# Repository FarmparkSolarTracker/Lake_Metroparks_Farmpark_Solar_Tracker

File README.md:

# Lake_Metroparks_Farmpark_Solar_Tracker
For more information, please see the wiki [here](https://github.com/FarmparkSolarTracker/Lake_Metroparks_Farmpark_Solar_Tracker/wiki).  

# Things which need work:
* Possible board issue where one side of the H-Bridges is unable to pull low, it only reaches High-Impedance
* Software for board is in a preliminary version, has not been fully tested due to the above issue
* A rough tester board has been included in the box, which theoretically can be used to send RS-485 commands to the main PCB. Code needs to be written for this device
* If the park has not done it yet, a new motor for the azimuth system must be ordered (it is believed that the worm gear is broken)
* The elevation linear actuator must be clamped in place
* Grommets must be put in place on the cables entering the new box
* Better data should be collected from the sensor, to better know how it operates

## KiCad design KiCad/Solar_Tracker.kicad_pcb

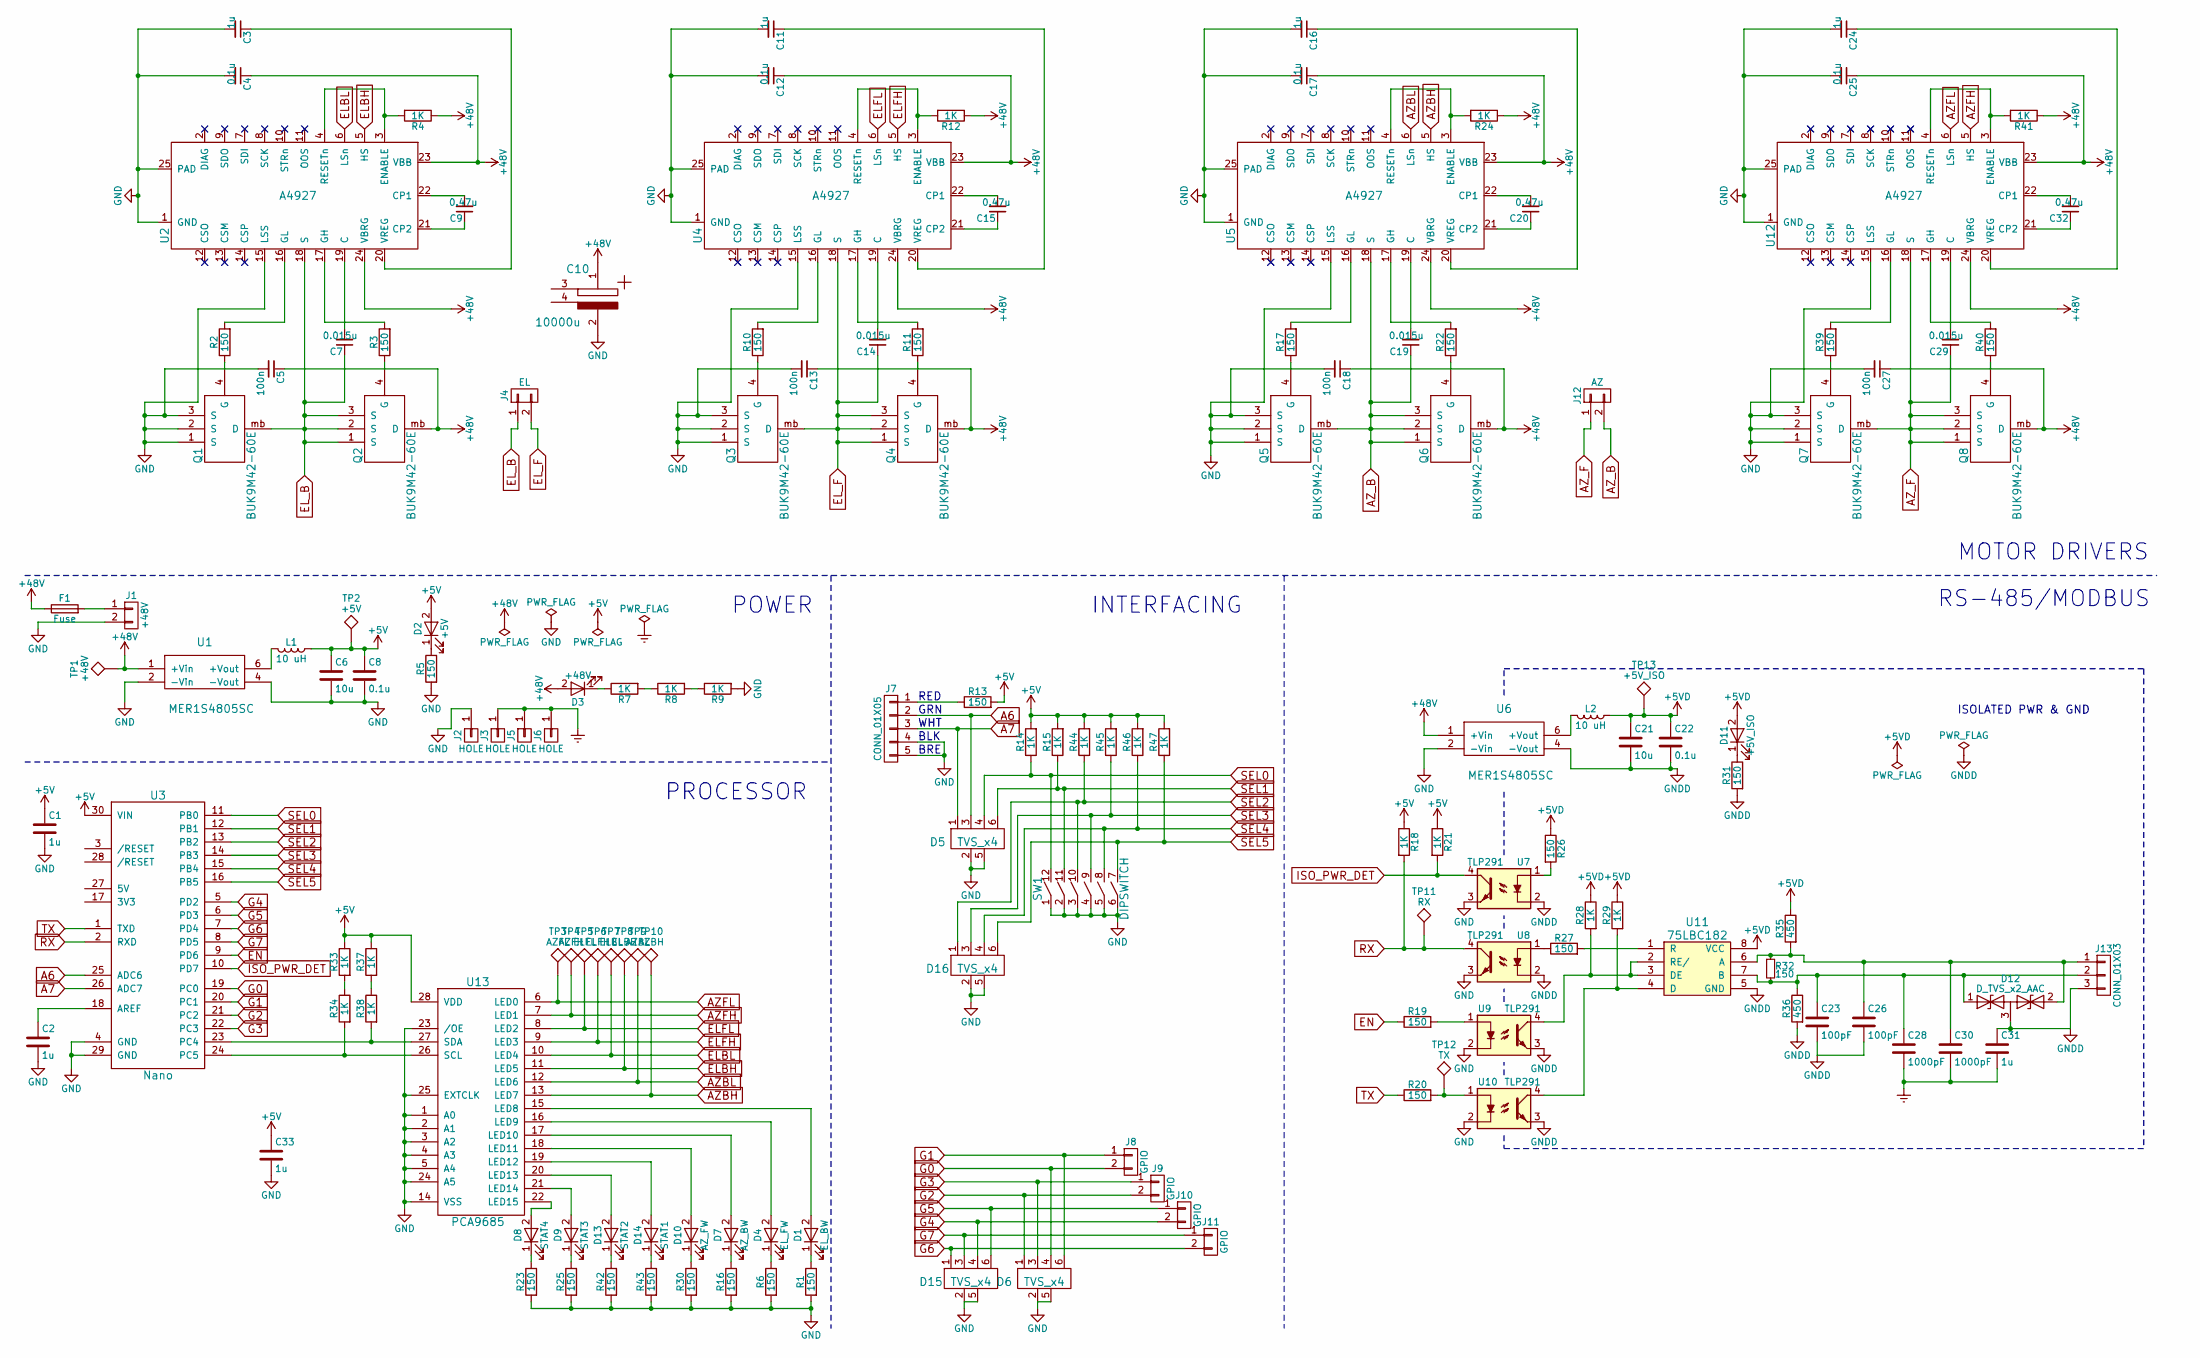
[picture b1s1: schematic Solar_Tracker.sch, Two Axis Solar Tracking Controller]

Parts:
C1, C2, C3, C11, C16, C24, C31, C33: 1u; C_0805
C4, C8, C12, C17, C22, C25: 0.1u; C_0805
C5, C13, C18, C27: 100n; C_0805
C6, C21: 10u; C_0805
C7, C14, C19, C29: 0.015u; C_0805
C9, C15, C20, C32: 0.47u; C_0805
C10: 10000u; vnd_cap
C23, C26: 100pF; C_0805
C28, C30: 1000pF; C_0805
D1: EL_BW; LED_1206_HandSoldering
D2: +5V; LED_1206_HandSoldering
D3: +48V; LED_1206_HandSoldering
D4: EL_FW; LED_1206_HandSoldering
D5, D6, D15, D16: TVS_x4; tvs_quad
D7: AZ_BW; LED_1206_HandSoldering
D8: STAT4; LED_1206_HandSoldering
D9: STAT3; LED_1206_HandSoldering
D10: AZ_FW; LED_1206_HandSoldering
D11: +5V_ISO; LED_1206_HandSoldering
D12: D_TVS_x2_AAC; SOT-23
D13: STAT2; LED_1206_HandSoldering
D14: STAT1; LED_1206_HandSoldering
F1: Fuse; R_Axial_DIN0204_L3.6mm_D1.6mm_P5.08mm_Horizontal
J1: +48V; PhoenixContact_GMSTBVA-G_02x7.50mm_Vertical
J2, J3, J5, J6: HOLE; M3
J4: EL; PhoenixContact_GMSTBVA-G_02x7.50mm_Vertical
J7: CONN_01X05; PhoenixContact_MCV-G_05x5.08mm_Vertical
J8, J9, J10, J11: GPIO; PhoenixContact_GMSTBVA-G_02x7.50mm_Vertical
J12: AZ; PhoenixContact_GMSTBVA-G_02x7.50mm_Vertical
J13: CONN_01X03; PhoenixContact_MCV-G_03x5.08mm_Vertical
L1, L2: 10 uH; L_1206_HandSoldering
Q1, Q2, Q3, Q4, Q5, Q6, Q7, Q8: BUK9M42-60E; nFET
R1, R2, R3, R5, R6, R10, R11, R13, R16, R17, R19, R20, R22, R23, R25, R26, R27, R30, R31, R32, R39, R40, R42, R43: 150; R_0805
R4, R7, R8, R9, R12, R14, R15, R18, R21, R24, R28, R29, R33, R34, R37, R38, R41, R44, R45, R46, R47: 1K; R_0805
R35, R36: 450; R_0805
SW1: DIPSWITCH; DIP-12_W7.62mm
TP1: +48V; test_pad
TP2: +5V; test_pad
TP3: AZFL; test_pad
TP4: AZFH; test_pad
TP5: ELFL; test_pad
TP6: ELFH; test_pad
TP7: ELBL; test_pad
TP8: ELBH; test_pad
TP9: AZBL; test_pad
TP10: AZBH; test_pad
TP11: RX; test_pad
TP12: TX; test_pad
TP13: +5V_ISO; test_pad
U1, U6: MER1S4805SC; 5v_iso
U2, U4, U5, U12: A4927; TSSOP-24_4.4x7.8mm_Pitch0.65mm
U3: Nano; Arduino_Nano
U7, U8, U9, U10: TLP291; opto
U11: 75LBC182; DIP-8_W7.62mm
U13: PCA9685; TSSOP-28_4.4x9.7mm_Pitch0.65mm

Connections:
+5V: C1.1, C6.1, C8.1, C33.1, D2.2 (A), L1.1, R13.2, R14.2, R15.2, R18.1, R21.1, R33.1, R37.1, R44.2, R45.2, R46.2, R47.2, TP2.1, U3.30 (VIN), U13.28 (VDD)
+5VD: C21.1, C22.1, D11.2 (A), L2.1, R26.1, R28.1, R29.1, R35.1, TP13.1, U11.8 (VCC)
+48V: C4.1, C5.1, C10.1, C12.1, C13.1, C17.1, C18.1, C25.1, C27.1, D3.2 (A), F1.1, Q2.mb (D), Q4.mb (D), Q6.mb (D), Q8.mb (D), R4.1, R12.1, R24.1, R41.1, TP1.1, U1.1 (+Vin), U2.23 (VBB), U2.24 (VBRG), U4.23 (VBB), U4.24 (VBRG), U5.23 (VBB), U5.24 (VBRG), U6.1 (+Vin), U12.23 (VBB), U12.24 (VBRG)
A6: D5.3, J7.2, U3.25 (ADC6)
A7: D5.1, J7.3, U3.26 (ADC7)
AZBH: TP10.1, U5.5 (HS), U13.13 (LED7)
AZBL: TP9.1, U5.6 (LSn), U13.12 (LED6)
AZFH: TP4.1, U12.5 (HS), U13.7 (LED1)
AZFL: TP3.1, U12.6 (LSn), U13.6 (LED0)
AZ_B: C19.1, J12.2, Q5.mb (D), Q6.1 (S), Q6.2 (S), Q6.3 (S), U5.18 (S)
AZ_F: C29.1, J12.1, Q7.mb (D), Q8.1 (S), Q8.2 (S), Q8.3 (S), U12.18 (S)
ELBH: TP8.1, U2.5 (HS), U13.11 (LED5)
ELBL: TP7.1, U2.6 (LSn), U13.10 (LED4)
ELFH: TP6.1, U4.5 (HS), U13.9 (LED3)
ELFL: TP5.1, U4.6 (LSn), U13.8 (LED2)
EL_B: C7.1, J4.1, Q1.mb (D), Q2.1 (S), Q2.2 (S), Q2.3 (S), U2.18 (S)
EL_F: C14.1, J4.2, Q3.mb (D), Q4.1 (S), Q4.2 (S), Q4.3 (S), U4.18 (S)
EN: R19.1, U3.9 (PD6)
Earth: C28.2, C30.2, C31.2, J3.1, J5.1, J6.1
G0: D6.4, J8.2, U3.19 (PC0)
G1: D6.6, J8.1, U3.20 (PC1)
G2: D6.1, J9.2, U3.21 (PC2)
G3: D6.3, J9.1, U3.22 (PC3)
G4: D15.4, J10.2, U3.5 (PD2)
G5: D15.6, J10.1, U3.6 (PD3)
G6: D15.1, J11.2, U3.7 (PD4)
G7: D15.3, J11.1, U3.8 (PD5)
GND: C1.2, C2.2, C3.2, C4.2, C5.2, C6.2, C8.2, C10.2, C11.2, C12.2, C13.2, C16.2, C17.2, C18.2, C24.2, C25.2, C27.2, C33.2, D5.2, D5.5, D6.2, D6.5, D15.2, D15.5, D16.2, D16.5, J1.2, J2.1, J7.4, J7.5, Q1.1 (S), Q1.2 (S), Q1.3 (S), Q3.1 (S), Q3.2 (S), Q3.3 (S), Q5.1 (S), Q5.2 (S), Q5.3 (S), Q7.1 (S), Q7.2 (S), Q7.3 (S), R1.2, R5.2, R6.2, R9.2, R16.2, R23.2, R25.2, R30.2, R42.2, R43.2, SW1.1, SW1.2, SW1.3, SW1.4, SW1.5, SW1.6, U1.2 (-Vin), U1.4 (-Vout), U2.1 (GND), U2.15 (LSS), U2.25 (PAD), U3.4 (GND), U3.29 (GND), U4.1 (GND), U4.15 (LSS), U4.25 (PAD), U5.1 (GND), U5.15 (LSS), U5.25 (PAD), U6.2 (-Vin), U7.3, U8.3, U9.2, U10.2, U12.1 (GND), U12.15 (LSS), U12.25 (PAD), U13.1 (A0), U13.2 (A1), U13.3 (A2), U13.4 (A3), U13.5 (A4), U13.14 (VSS), U13.23 (/OE), U13.24 (A5), U13.25 (EXTCLK)
GNDD: C21.2, C22.2, C23.2, C26.2, C31.1, D12.3 (common), J13.3, R31.2, R36.2, U6.4 (-Vout), U7.2, U8.2, U9.3, U10.3, U11.5 (GND)
ISO_PWR_DET: R21.2, U3.10 (PD7), U7.4
unnamed: C2.1, U3.18 (AREF)
unnamed: C3.1, U2.20 (VREG)
unnamed: C7.2, U2.19 (C)
unnamed: C9.1, U2.21 (CP2)
unnamed: C9.2, U2.22 (CP1)
unnamed: C11.1, U4.20 (VREG)
unnamed: C14.2, U4.19 (C)
unnamed: C15.1, U4.21 (CP2)
unnamed: C15.2, U4.22 (CP1)
unnamed: C16.1, U5.20 (VREG)
unnamed: C19.2, U5.19 (C)
unnamed: C20.1, U5.21 (CP2)
unnamed: C20.2, U5.22 (CP1)
unnamed: C23.1, C28.1, D12.1 (A1), J13.2, R32.2, R36.1, U11.7 (B)
unnamed: C24.1, U12.20 (VREG)
unnamed: C26.1, C30.1, D12.2 (A2), J13.1, R32.1, R35.2, U11.6 (A)
unnamed: C29.2, U12.19 (C)
unnamed: C32.1, U12.21 (CP2)
unnamed: C32.2, U12.22 (CP1)
unnamed: D1.1 (K), R1.1
unnamed: D1.2 (A), U13.15 (LED8)
unnamed: D2.1 (K), R5.1
unnamed: D3.1 (K), R7.1
unnamed: D4.1 (K), R6.1
unnamed: D4.2 (A), U13.16 (LED9)
unnamed: D7.1 (K), R16.1
unnamed: D7.2 (A), U13.17 (LED10)
unnamed: D8.1 (K), R23.1
unnamed: D8.2 (A), U13.22 (LED15)
unnamed: D9.1 (K), R25.1
unnamed: D9.2 (A), U13.21 (LED14)
unnamed: D10.1 (K), R30.1
unnamed: D10.2 (A), U13.18 (LED11)
unnamed: D11.1 (K), R31.1
unnamed: D13.1 (K), R42.1
unnamed: D13.2 (A), U13.20 (LED13)
unnamed: D14.1 (K), R43.1
unnamed: D14.2 (A), U13.19 (LED12)
unnamed: F1.2, J1.1
unnamed: J7.1, R13.1
unnamed: L1.2, U1.6 (+Vout)
unnamed: L2.2, U6.6 (+Vout)
unnamed: Q1.4 (G), R2.1
unnamed: Q2.4 (G), R3.1
unnamed: Q3.4 (G), R10.1
unnamed: Q4.4 (G), R11.1
unnamed: Q5.4 (G), R17.1
unnamed: Q6.4 (G), R22.1
unnamed: Q7.4 (G), R39.1
unnamed: Q8.4 (G), R40.1
unnamed: R2.2, U2.16 (GL)
unnamed: R3.2, U2.17 (GH)
unnamed: R4.2, U2.3 (ENABLE), U2.4 (RESETn)
unnamed: R7.2, R8.1
unnamed: R8.2, R9.1
unnamed: R10.2, U4.16 (GL)
unnamed: R11.2, U4.17 (GH)
unnamed: R12.2, U4.3 (ENABLE), U4.4 (RESETn)
unnamed: R17.2, U5.16 (GL)
unnamed: R19.2, U9.1
unnamed: R20.2, TP12.1, U10.1
unnamed: R22.2, U5.17 (GH)
unnamed: R24.2, U5.3 (ENABLE), U5.4 (RESETn)
unnamed: R26.2, U7.1
unnamed: R27.1, U8.1
unnamed: R27.2, U11.1 (R)
unnamed: R28.2, U9.4, U11.2 (RE/), U11.3 (DE)
unnamed: R29.2, U10.4, U11.4 (D)
unnamed: R33.2, R34.1
unnamed: R34.2, U3.24 (PC5), U13.26 (SCL)
unnamed: R37.2, R38.1
unnamed: R38.2, U3.23 (PC4), U13.27 (SDA)
unnamed: R39.2, U12.16 (GL)
unnamed: R40.2, U12.17 (GH)
unnamed: R41.2, U12.3 (ENABLE), U12.4 (RESETn)
RX: R18.2, TP11.1, U3.2 (RXD), U8.4
SEL0: D5.4, R14.1, SW1.12, U3.11 (PB0)
SEL1: D5.6, R15.1, SW1.11, U3.12 (PB1)
SEL2: D16.1, R44.1, SW1.10, U3.13 (PB2)
SEL3: D16.3, R45.1, SW1.9, U3.14 (PB3)
SEL4: D16.4, R46.1, SW1.8, U3.15 (PB4)
SEL5: D16.6, R47.1, SW1.7, U3.16 (PB5)
TX: R20.1, U3.1 (TXD)

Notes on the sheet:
ISOLATED PWR & GND
POWER
PROCESSOR
INTERFACING
RS-485/MODBUS
MOTOR DRIVERS
RED
GRN
WHT
BLK
BRE

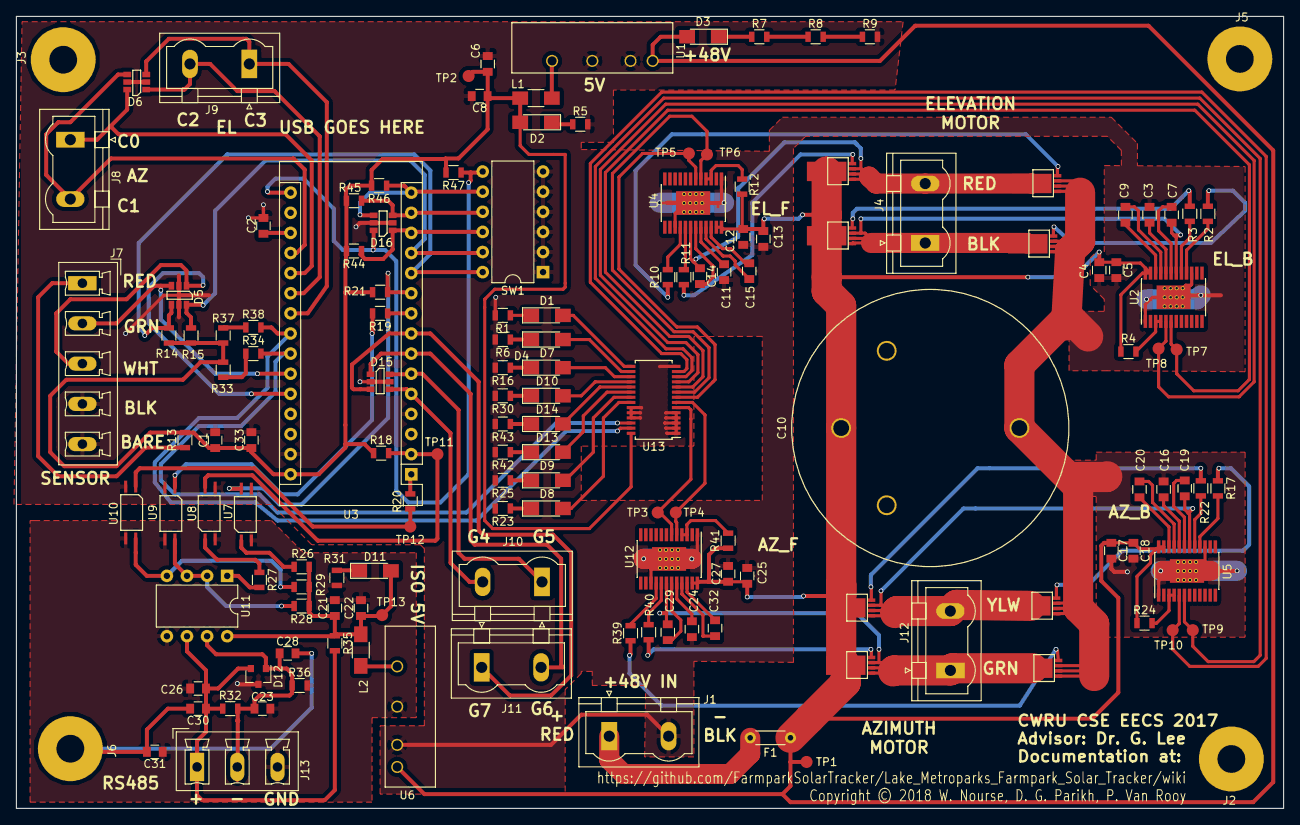
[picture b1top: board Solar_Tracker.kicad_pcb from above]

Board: 2 copper layers, 160.0 x 100.0 mm, 147 parts (0 on the bottom side), 113 nets.

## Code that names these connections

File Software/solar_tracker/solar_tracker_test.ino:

#include <Wire.h>

/*
 * Farmpark Solar Tracker
 * © William Nourse, Darshan G. Parikh, Paula Van Rooy 2017
 */
#include <Adafruit_PWMServoDriver.h>

//declare pwm driver object
Adafruit_PWMServoDriver pwm = Adafruit_PWMServoDriver();

//expander pin numbers of motor drivers
int AZ_FL = 0;
int AZ_FH = 1;
int AZ_BL = 6;
int AZ_BH = 7;
int EL_FL = 2;
int EL_FH = 3;
int EL_BL = 4;
int EL_BH = 5;

//expander pin numbers of LEDs
int LED_ELB = 8;
int LED_ELF = 9;
int LED_AZB = 10;
int LED_AZF = 11;
int LED_ST1 = 12;
int LED_ST2 = 13;
int LED_ST3 = 14;
int LED_ST4 = 15;

//config switch pins
int SEL0 = 8;
int SEL1 = 9;
int SEL2 = 10;
int SEL3 = 11;
int SEL4 = 12;
int SEL5 = 13;

//speed temp variables
int az36 = 0;
int az48 = 0;
int el36 = 0;
int el48 = 0;

int azSpeed = 2048;
int azNeg = 2048;
int elSpeed = 2048;
int elNeg = 2048;

void setup() {
  //initialize expander communication
  pwm.begin();
  pwm.setPWMFreq(60); //Hz

  //Pinmodes
  pinMode(SEL0, INPUT);
  pinMode(SEL1, INPUT);
  pinMode(SEL2, INPUT);
  pinMode(SEL3, INPUT);
  pinMode(SEL4, INPUT);
  pinMode(SEL5, INPUT);

  az36 = digitalRead(SEL0);
  az48 = digitalRead(SEL1);
  el36 = digitalRead(SEL2);
  el48 = digitalRead(SEL4);

  //Set azimuth motor scaling from switches
  if (az48 == HIGH){
    azSpeed = 4096;
    pwm.setPWM(LED_ST1,4096,0);
  }else if (az36 == HIGH){
    azSpeed = 3072;
    pwm.setPWM(LED_ST2,4096,0);
  }else{
    azSpeed = 2048;
  }
  //Set elevation motor scaling from switches
  if (el48 == HIGH){
    elSpeed = 4096;
    pwm.setPWM(LED_ST3,4096,0);
  }else if (el36 == HIGH){
    elSpeed = 3072;
    pwm.setPWM(LED_ST4,4096,0);
  }else{
    elSpeed = 2048;
  }
  azNeg = 4096 - azSpeed;
  elNeg = 4096 - elSpeed;

}

void loop() {
  ctrlMotor(false,true);  //el_fw light, jack shit
  ctrlMotor(true,true);  //az_fw light, jack shit
  delay(1000);
  //freezeMotor();
  //delay(1000);
  //ctrlMotor(true,false);  //az_bw light, az_bw drive
  //ctrlMotor(false,false); //el_bw light, el_bw drive
  //delay(1000);
  freezeMotor();
  //freezeMotor();
  delay(1000);
}

void ctrlMotor(bool az, bool fwd){
  if (az == true){
    if (fwd == true){
      pwm.setPWM(AZ_FH,azSpeed,azNeg);
      pwm.setPWM(LED_AZF,azSpeed,azNeg);
      pwm.setPWM(AZ_FL,4096,0);
      pwm.setPWM(AZ_BH,0,4096);
      pwm.setPWM(AZ_BL,0,4096);
    }else{
      pwm.setPWM(AZ_FH,0,4096);
      pwm.setPWM(AZ_FL,0,4096);
      pwm.setPWM(AZ_BH,azSpeed,azNeg);
      pwm.setPWM(LED_AZB,azSpeed,azNeg);
      pwm.setPWM(AZ_BL,4096,0);
    }
  }else{
    if (fwd == true){
      pwm.setPWM(EL_FH,elSpeed,elNeg);
      pwm.setPWM(LED_ELF,elSpeed,elNeg);
      pwm.setPWM(EL_FL,4096,0);
      pwm.setPWM(EL_BH,0,4096);
      pwm.setPWM(EL_BL,0,4096);
    }else{
      pwm.setPWM(EL_FH,0,4096);
      pwm.setPWM(EL_FL,0,4096);
      pwm.setPWM(EL_BH,elSpeed,elNeg);
      pwm.setPWM(LED_ELB,elSpeed,elNeg);
      pwm.setPWM(EL_BL,4096,0);
    }
  }
}

void freezeMotor(){
    pwm.setPWM(AZ_FH,0,4096);
    pwm.setPWM(AZ_FL,0,4096);
    pwm.setPWM(AZ_BH,0,4096);
    pwm.setPWM(AZ_BL,0,4096);
    pwm.setPWM(LED_AZF,0,4096);
    pwm.setPWM(LED_AZB,0,4096);
    pwm.setPWM(EL_FH,0,4096);
    pwm.setPWM(EL_FL,0,4096);
    pwm.setPWM(EL_BH,0,4096);
    pwm.setPWM(EL_BL,0,4096);
    pwm.setPWM(LED_ELF,0,4096);
    pwm.setPWM(LED_ELB,0,4096);
}

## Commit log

2017-09-09 Started work on schematic
2017-09-17 Replaced optos and bus transceiver with through-hole versions
2017-09-21 added
2017-09-21 Added FTDI chip to library, added Atmega328 to schematic
2017-09-21 added connections to FTDI chip
2017-09-22 made the schematic
2017-09-22 Paula's Changes
2017-09-22 Paula's update for power
2017-09-22 Update to add symbol 32U4 to schematic
2017-09-22 Added passives library
2017-09-22 Added isolation marking for RS-485
2017-09-22 Added USB hardware to ATMEGA32u4 symbol
2017-09-22 Added power connections and bypass caps to 32u4
2017-09-22 Added all port names for 32u4
2017-09-23 Set resistor values, added status LEDs, and added resonator
2017-09-23 Rearranged blocks of schematic
2017-09-25 Added to library and schematic for gate drivers and H-bridges. Still need to confirm gate driver capacitor values. Also, rearranged overall schematic for neatness. May need to adjust slightly to acco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
2017-09-25 Rearranged into blocks, added visual indicator lines
2017-09-25 Added power flags
2017-09-25 Added motor capacitors
2017-09-26 Updated pullups on config jumpers
2017-09-28 Annotated
2017-09-29 Redid analog connector
2017-09-29 Added pdf version
2017-10-03 New motor cap values
2017-10-03 Paired with footprints
2017-10-03 Added nFET footprint
2017-10-04 Changed 5v filter caps
2017-10-04 Associated footprints
2017-10-05 Added title block info
2017-10-05 Added footprints for TVS diodes
2017-10-05 Added resonator footprint
2017-10-05 Added regulator and capacitor footprints, and modified symbol for large capacitor
2017-10-05 Updated capacitor symbol in schematic, updated linkings between components and symbols
2017-10-05 Added mounting hole footprint, tied to hole symbol
2017-10-05 Spread out components on PCB
2017-10-05 Updated switch symbol, added nFET landings to pcb
2017-10-05 Updated symbols for TVS_USB and the motor driver
2017-10-05 All components in PCB
2017-10-06 Work on grouping components
2017-10-06 components organized
2017-10-06 saved changes
2017-10-10 Started work on layout
2017-10-10 more layout work
2017-10-12 Layout updates
2017-10-12 Updated schematic to use Nano, added Nano part
2017-10-12 Updated annotation
2017-10-12 Fixing library issues
2017-10-12 Added nano footprint
2017-10-12 Exported netlist
2017-10-12 Updated netlist in pcb
2017-10-12 Fixed CvPCB
2017-10-13 updates to pcb
2017-10-13 attempt 1 at motor layout
2017-10-13 more updates
2017-10-13 updates again
2017-10-13 regrouping in process
2017-10-13 all components regrouped
2017-10-13 motor work
2017-10-15 layout work
2017-10-15 interfacing/rs485 version 1 complete
2017-10-15 initial layout
2017-10-16 Layout prelim not RS-485
2017-10-17 Rearranged connectors, reassigned mounting hole power
2017-10-17 Fixed connector issues
2017-10-17 motor updates
2017-10-17 Updated source connections
2017-10-17 Tuesday layout changes - motors and notes
2017-10-19 redone motor layout
2017-10-19 Version 2 layout complete
2017-10-19 Fixes for Paula
2017-10-19 Saved fixes
2017-10-20 Reviewed layout with J.G. - approved
2017-10-22 Ver. 3 RS-485-done
2017-10-24 interfacing/processor Ver. 3 complete, motor in progress
2017-10-24 Fixed ground for Paula
2017-10-25 motor layout updates
2017-10-25 planes and motor updates
2017-10-26 added planes and updates
2017-10-26 silkscreen updates
2017-10-26 added planes
2017-10-26 made the ratsnest go away
2017-10-26 Silky smooth ;)
2017-10-26 updated RS-485
2017-10-26 gerbers
2017-11-10 Started software
2017-11-10 Implemented initializations, and main loop
2017-11-12 added photo for wiki
2017-11-12 Fixed driver footprint
2017-11-12 Imported netlist
2017-11-12 Fixed connectors
2017-11-12 Added pwm expander symbol
2017-11-12 Added expander to pcb
2017-11-13 updates to layout due to new footprints. Gave space to power, fixed connectors, began motors
2017-11-13 Fixed pinout for paula
2017-11-13 continued with motors and new layout
2017-11-13 Updated schematic for Paula
2017-11-13 Same stuff, different day
2017-11-16 Created the link to the wiki
2017-12-07 Reintegration
2018-08-23 Updated documentation
2018-08-24 Finished documentation

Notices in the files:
KiCad/Solar_Tracker.kicad_pcb:
Copyright © 2018 W. Nourse, D. G. Parikh, P. Van Rooy
